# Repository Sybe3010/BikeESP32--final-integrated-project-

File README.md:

## BIKE-ESP32
BikeEsp32 is a final project made by Sybe Van den Bergh.
I am a 16 year old student Informatica and Datacommunication Science.
Since this project has just started I will not accept any pull requests, I can accept this kind of requests as of July 2026 when I graduate.

## The Project
This project features a ESP32-S3 devkit equiped with 16MB ROM and 8MB PSRAM, to connect al sensor and actuators there is a PCB. The board is programmed using VSCode on PlatformIO. The chosen platform is Arduino meanly because that is what we use at school, but also because of the great support.
In the future I would like to expand the project and make a custom PCB.

## The Progress
- [X] Searching information
- [ ] Testing Maps
- [ ] Making home/settings screens
- [ ] Making activities
- [ ] Reading BLE sensors
- [ ] Documenting

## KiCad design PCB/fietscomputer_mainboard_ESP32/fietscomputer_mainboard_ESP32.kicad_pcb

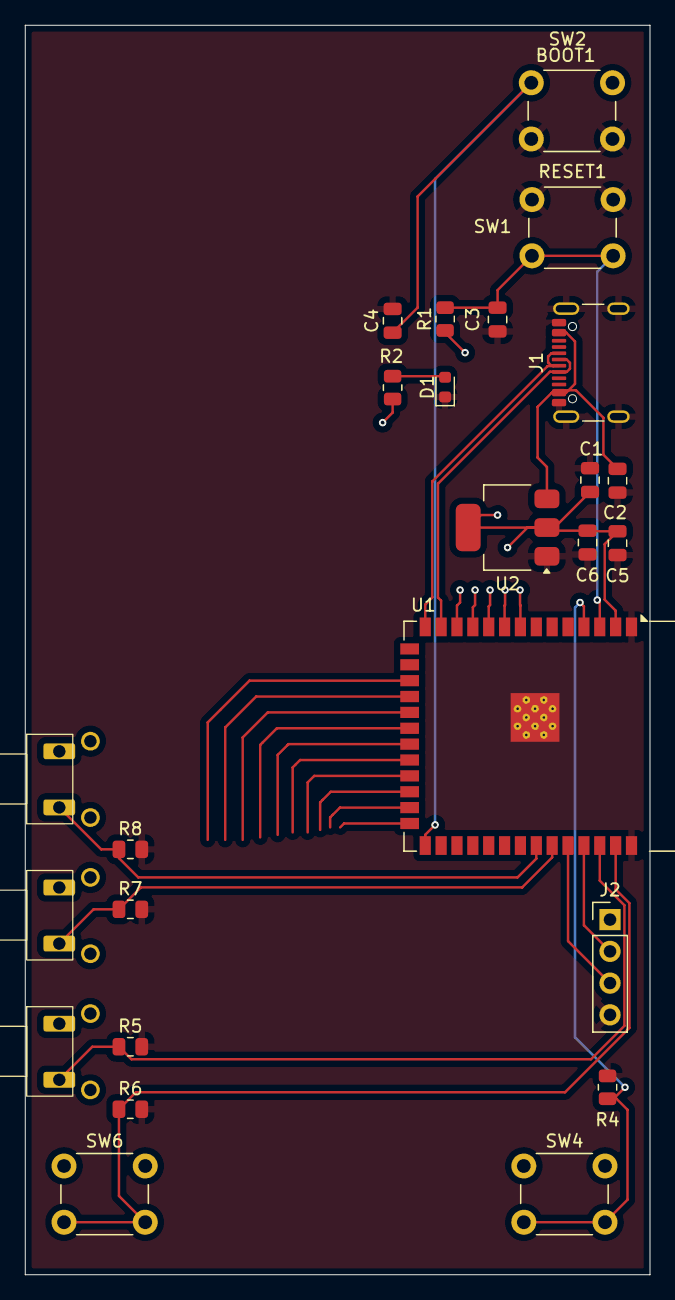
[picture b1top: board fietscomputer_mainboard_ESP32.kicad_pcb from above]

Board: 4 copper layers, 50.0 x 100.0 mm, 25 parts (0 on the bottom side), 15 nets.

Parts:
C1, C2, C6: 10uF; C_0805_2012Metric
C3, C4, C5: 0.1uF; C_0805_2012Metric
D1: POWER_LED; LED_0603_1608Metric
J1: USB_C_Receptacle_USB2.0_14P; USB_C_Receptacle_GCT_USB4105-xx-A_16P_TopMnt_Horizontal
J2: Conn_01x04_Pin; PinHeader_1x04_P2.54mm_Vertical
R1, R2, R4, R5, R6, R7, R8: 10K; R_0805_2012Metric
SW1: RESET1; SW_PUSH_6mm
SW2: BOOT1; SW_PUSH_6mm
SW4: PAGE_BUTTON; SW_PUSH_6mm
SW5: LAP_BUTTON; KNOP ANGLED
SW6: MAIN_BUTTON; SW_PUSH_6mm
SW7: ZOOM-_BUTTON; KNOP ANGLED
SW8: ZOOM+_BUTTON; KNOP ANGLED
U1: ESP32-S3-WROOM-1
U2: AMS1117-3.3; SOT-223-3_TabPin2

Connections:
+3.3V: C1.1, C5.1, C6.1, J2.1, R1.1, R2.1, SW4.1, SW5.1, SW6.1, SW7.1, SW8.1, U1.2 (3V3), U2.2 (VO)
GND: C1.2, C2.2, C3.2, C4.2, C5.2, C6.2, D1.1 (K), J1.A1 (GND), J1.A12 (GND), J1.B1 (GND), J1.B12 (GND), J1.S1 (SHIELD), J2.4, R4.2, R5.2, R6.2, R7.2, R8.2, SW1.1, SW2.1, U1.1 (GND), U1.40 (GND), U1.41 (GND), U2.1 (GND)
IO1: C4.1, SW2.2, U1.27 (IO0)
LAP_BUTTON: R5.1, SW5.2, U1.38 (IO2)
MAIN_BUTTON: R6.1, SW6.2, U1.39 (IO1)
unnamed: D1.2 (A), R2.2
unnamed: C3.1, R1.2, SW1.2, U1.3 (EN)
PAGE_BUTTON: R4.1, SW4.2, U1.4 (IO4)
RX_GPS: J2.2, U1.37 (TXD0)
TX_GPS: J2.3, U1.36 (RXD0)
USB+: J1.A6 (D+), J1.B6 (D+), U1.14 (USB_D+)
USB-: J1.A7 (D-), J1.B7 (D-), U1.13 (USB_D-)
VBUS: C2.1, J1.A4 (VBUS), J1.A9 (VBUS), J1.B4 (VBUS), J1.B9 (VBUS), U2.3 (VI)
ZOOM+_BUTTON: R8.1, SW8.2, U1.34 (IO41)
ZOOM-_BUTTON: R7.1, SW7.2, U1.35 (IO42)

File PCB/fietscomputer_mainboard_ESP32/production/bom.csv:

Designator,Footprint,Quantity,Value,LCSC Part #
"C1, C2, C6",0805,3,10uF,
"C3, C4, C5",0805,3,0.1uF,
D1,0603,1,POWER_LED,
J1,USB_C_Receptacle_GCT_USB4105-xx-A_16P_TopMnt_Horizontal,1,USB_C_Receptacle_USB2.0_14P,
J2,PinHeader_1x04_P2.54mm_Vertical,1,Conn_01x04_Pin,
"R1, R2, R4, R5, R6, R7, R8",0805,7,10K,
SW1,SW_PUSH_6mm,1,RESET1,
SW2,SW_PUSH_6mm,1,BOOT1,
SW4,SW_PUSH_6mm,1,PAGE_BUTTON,
SW5,KNOP ANGLED,1,LAP_BUTTON,
SW6,SW_PUSH_6mm,1,MAIN_BUTTON,
SW7,KNOP ANGLED,1,ZOOM-_BUTTON,
SW8,KNOP ANGLED,1,ZOOM+_BUTTON,
U1,ESP32-S3-WROOM-1,1,ESP32-S3-WROOM-1,
U2,SOT-223-3_TabPin2,1,AMS1117-3.3,

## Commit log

2025-09-02 base upload
2025-09-02 base2
2025-09-04 create esp program
2025-09-07 TCX library met snelheid, power, candans en lap functionaliteit
2025-09-09 GPXParser
2025-10-23 new main
2025-10-31 Update GIP Sybe Van den Bergh.docx
    nieuwe versie, wegens corruptie oude
2025-11-05 homescreen gemaakt
2025-11-05 extra inhoud settingstile gemaakt
